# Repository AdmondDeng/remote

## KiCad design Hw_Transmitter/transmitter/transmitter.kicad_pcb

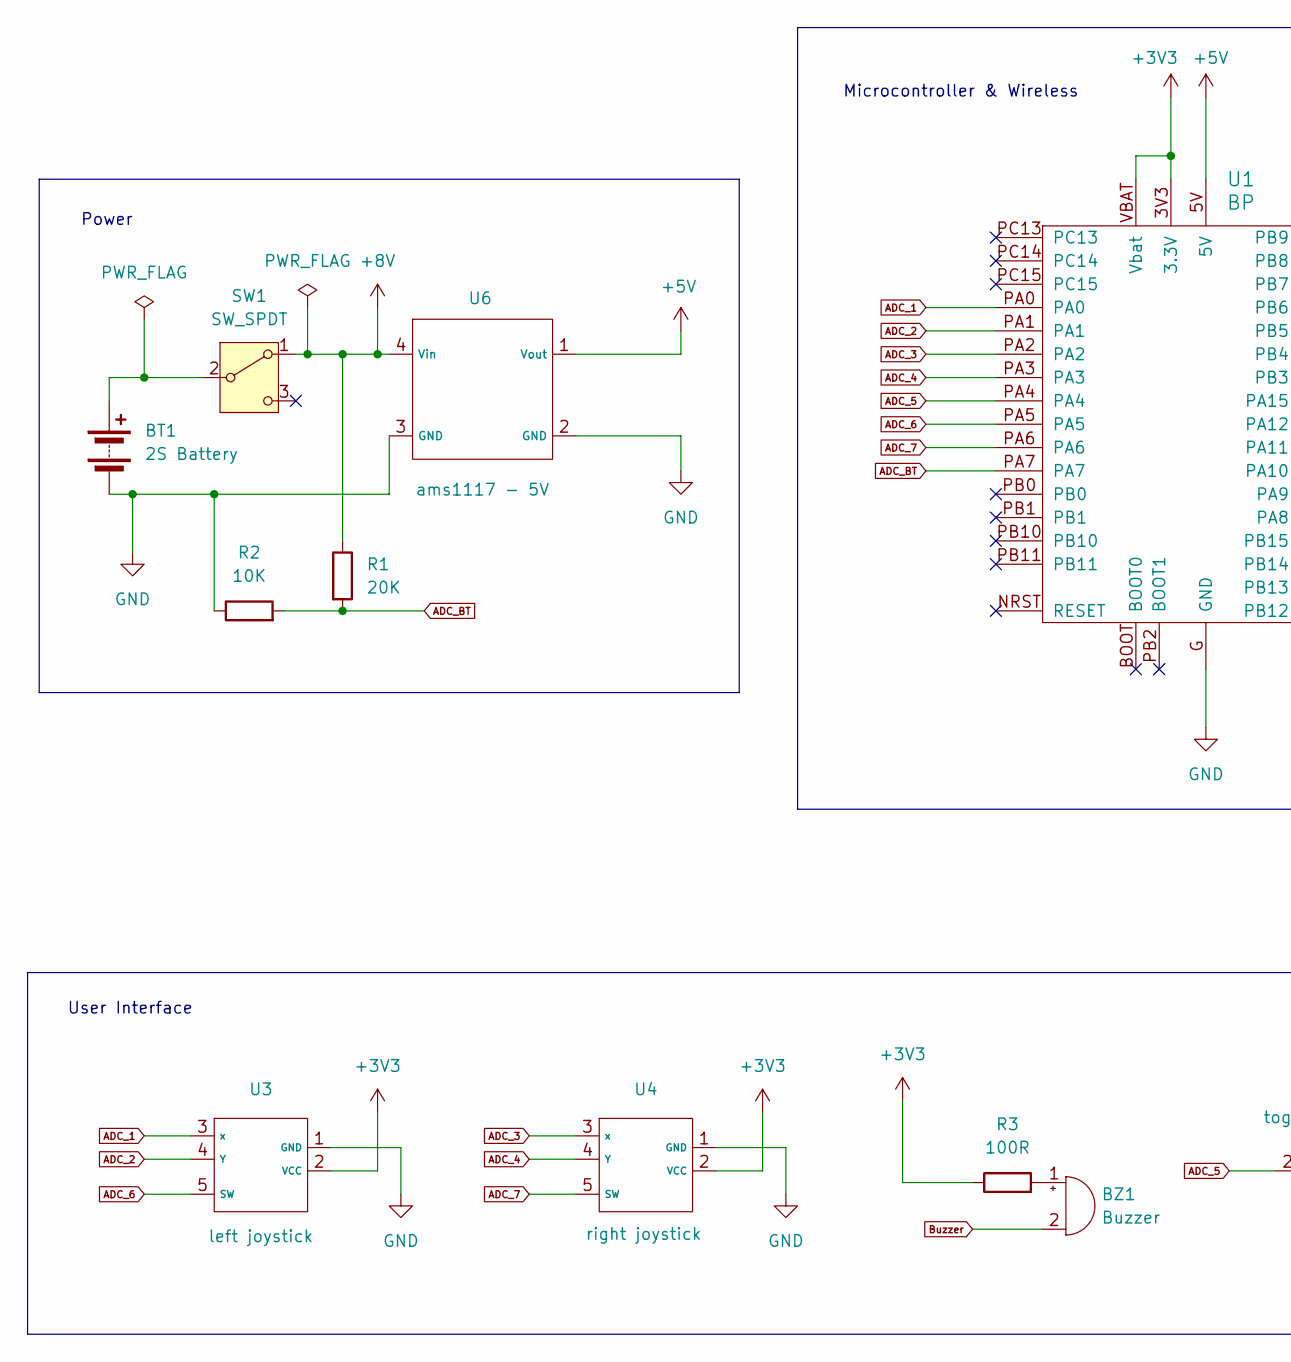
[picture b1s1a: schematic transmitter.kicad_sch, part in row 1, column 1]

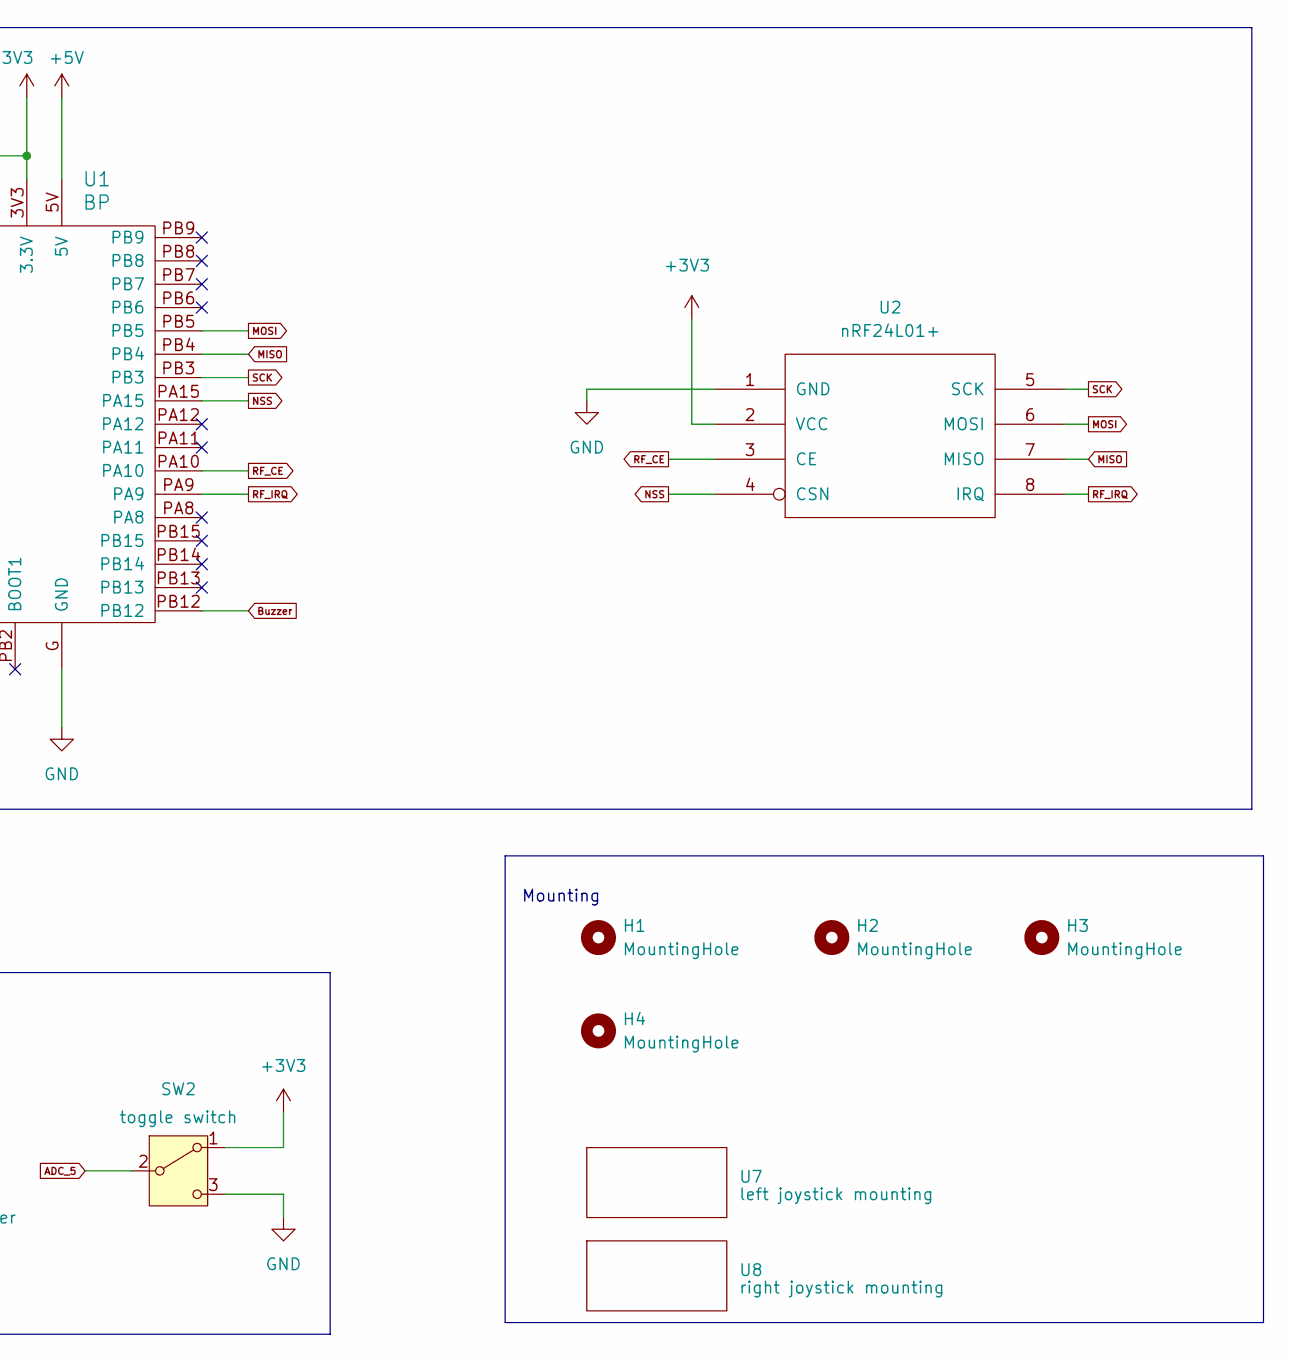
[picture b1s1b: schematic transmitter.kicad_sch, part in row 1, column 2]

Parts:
BT1: 2S Battery; R_2816_7142Metric_Pad3.20x4.45mm_HandSolder
BZ1: Buzzer; buzzer
H1, H2, H3, H4: MountingHole; MountingHole_3.2mm_M3
R1: 20K; R_Axial_DIN0207_L6.3mm_D2.5mm_P10.16mm_Horizontal
R2: 10K; R_Axial_DIN0207_L6.3mm_D2.5mm_P10.16mm_Horizontal
R3: 100R; R_Axial_DIN0207_L6.3mm_D2.5mm_P10.16mm_Horizontal
SW1: SW_SPDT; toggle_switch
SW2: toggle switch; toggle_switch
U1: BP; blue_pill
U2: nRF24L01+; PinHeader_2x04_P2.54mm_Vertical
U3: left joystick; PinHeader_1x05_P2.54mm_Vertical
U4: right joystick; PinHeader_1x05_P2.54mm_Vertical
U6: ams1117 - 5V; ams1117_module
U7: left joystick mounting; joystick_mounting
U8: right joystick mounting; joystick_mounting

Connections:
+3V3: R3.1, SW2.1 (A), U1.3V3 (3.3V), U1.VBAT (Vbat), U2.2 (VCC), U3.2 (VCC), U4.2 (VCC)
+5V: U1.5V, U6.1 (Vout)
+8V: R1.1, SW1.1 (A), U6.4 (Vin)
ADC_1: U1.PA0, U3.3 (x)
ADC_2: U1.PA1, U3.4 (Y)
ADC_3: U1.PA2, U4.3 (x)
ADC_4: U1.PA3, U4.4 (Y)
ADC_5: SW2.2 (B), U1.PA4
ADC_6: U1.PA5, U3.5 (SW)
ADC_7: U1.PA6, U4.5 (SW)
ADC_BT: R1.2, R2.2, U1.PA7
Buzzer: BZ1.2 (-), U1.PB12
GND: BT1.2 (-), R2.1, SW2.3 (C), U1.G (GND), U2.1 (GND), U3.1 (GND), U4.1 (GND), U6.2 (GND), U6.3 (GND)
MISO: U1.PB4, U2.7 (MISO)
MOSI: U1.PB5, U2.6 (MOSI)
NSS: U1.PA15, U2.4 (CSN)
unnamed: BT1.1 (+), SW1.2 (B)
unnamed: BZ1.1 (+), R3.2
RF_CE: U1.PA10, U2.3 (CE)
RF_IRQ: U1.PA9, U2.8 (IRQ)
SCK: U1.PB3, U2.5 (SCK)

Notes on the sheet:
Power
Microcontroller & Wireless
User Interface
Mounting

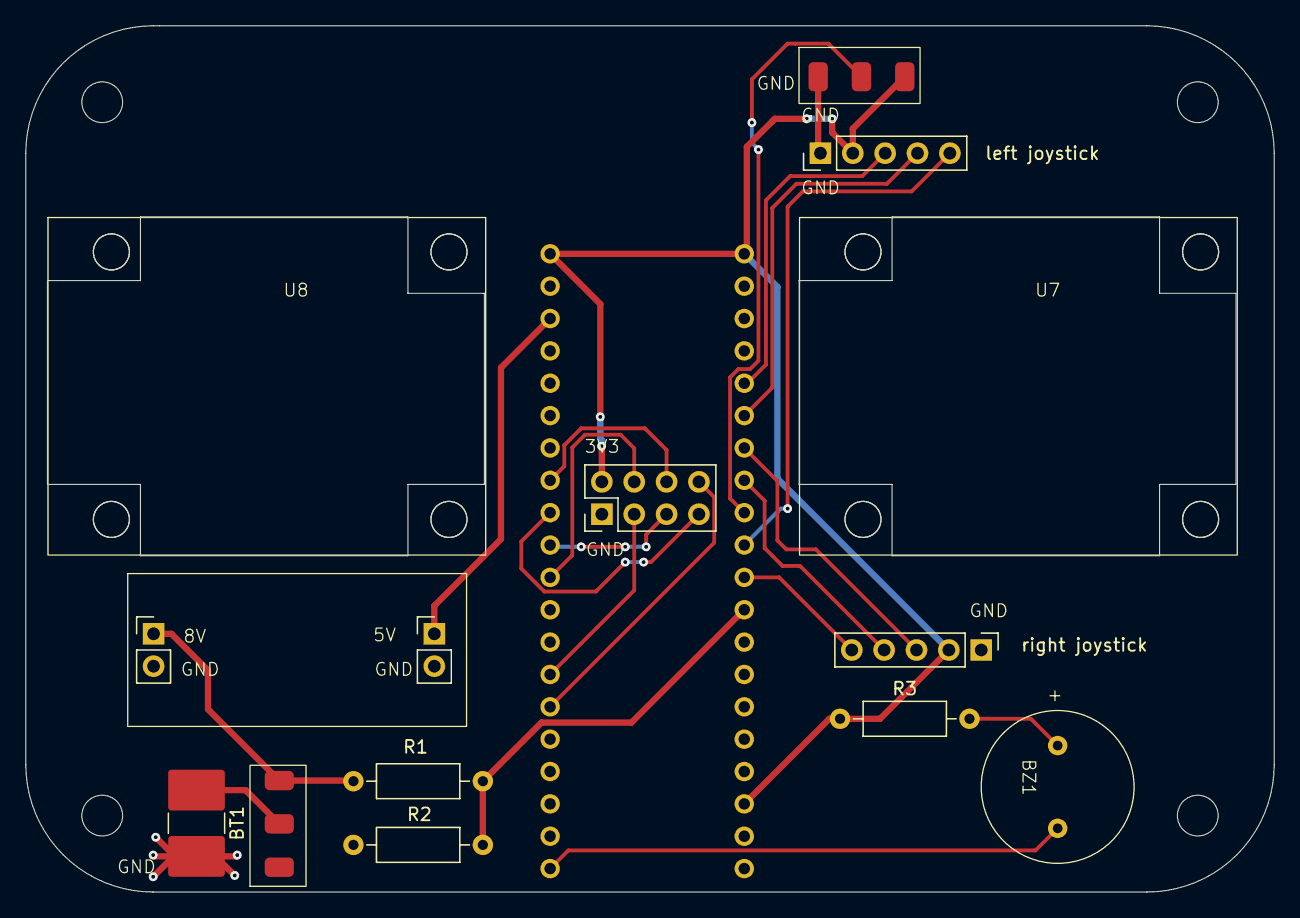
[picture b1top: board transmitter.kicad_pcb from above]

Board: 2 copper layers, 98.0 x 68.0 mm, 18 parts (1 on the bottom side), 21 nets.

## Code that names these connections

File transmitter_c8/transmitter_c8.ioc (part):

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Mcu.Name=STM32F103C(8-B)Tx
Mcu.Package=LQFP48
Mcu.UserName=STM32F103C8Tx
PA0-WKUP.Signal=ADCx_IN0
PA1.Signal=ADCx_IN1
PA10.GPIOParameters=GPIO_Label
PA10.GPIO_Label=RF_CE
PA10.Signal=GPIO_Output
PA11.Mode=Device
PA11.Signal=USB_DM
PA12.Mode=Device
PA12.Signal=USB_DP
PA13.Mode=Serial_Wire
PA13.Signal=SYS_JTMS-SWDIO
PA14.Mode=Serial_Wire
PA14.Signal=SYS_JTCK-SWCLK
PA15.GPIOParameters=PinState,GPIO_Label
PA15.GPIO_Label=NSS
PA15.PinState=GPIO_PIN_SET
PA15.Signal=GPIO_Output
PA2.Signal=ADCx_IN2
PA3.Signal=ADCx_IN3
PA4.Signal=ADCx_IN4
PA5.Signal=ADCx_IN5
PA6.Signal=ADCx_IN6
PA7.Signal=ADCx_IN7
PA9.GPIOParameters=GPIO_Label,GPIO_ModeDefaultEXTI
PA9.GPIO_Label=RF_IRQ
PA9.GPIO_ModeDefaultEXTI=GPIO_MODE_IT_FALLING
PA9.Signal=GPXTI9
PB10.GPIOParameters=GPIO_Label
PB10.GPIO_Label=Test
PB10.Signal=GPIO_Output
PB12.GPIOParameters=GPIO_Label
PB12.GPIO_Label=Buzzer
PB12.Signal=GPIO_Output
PB3.Mode=Full_Duplex_Master
PB3.Signal=SPI1_SCK
PB4.Mode=Full_Duplex_Master
PB4.Signal=SPI1_MISO
PB5.Mode=Full_Duplex_Master
PB5.Signal=SPI1_MOSI
PC13-TAMPER-RTC.GPIOParameters=GPIO_Label
PC13-TAMPER-RTC.GPIO_Label=LED
PC13-TAMPER-RTC.Signal=GPIO_Output
PC14-OSC32_IN.Mode=LSE-External-Oscillator
PC14-OSC32_IN.Signal=RCC_OSC32_IN
PC15-OSC32_OUT.Mode=LSE-External-Oscillator
PC15-OSC32_OUT.Signal=RCC_OSC32_OUT
PD0-OSC_IN.Mode=HSE-External-Oscillator
PD0-OSC_IN.Signal=RCC_OSC_IN
PD1-OSC_OUT.Mode=HSE-External-Oscillator
PD1-OSC_OUT.Signal=RCC_OSC_OUT
RCC.SYSCLKFreq_VALUE=48000000
RCC.SYSCLKSource=RCC_SYSCLKSOURCE_PLLCLK
board=custom

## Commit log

2024-06-27 1. transmitter: replace ams1117-3.3V with ams1117-5V. 2. remove backup files and update git ignore file.
2024-06-28 bug fix for nrf24l01p library.
2024-06-30 for transmitter: buzz when battery voltage goes below 6.6V
